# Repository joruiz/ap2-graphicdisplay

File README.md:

ap2-graphicdisplay
==================

Graphic display module for the Agile Prototyping Platform

  This work has been supported by project grant CEN-20101019 (THOFU), funded
by the Spanish Centro para el Desarrollo Tecnol ogico Industrial (CDTI) and
supported by the Spanish Ministerio de Economía y Competitividad.

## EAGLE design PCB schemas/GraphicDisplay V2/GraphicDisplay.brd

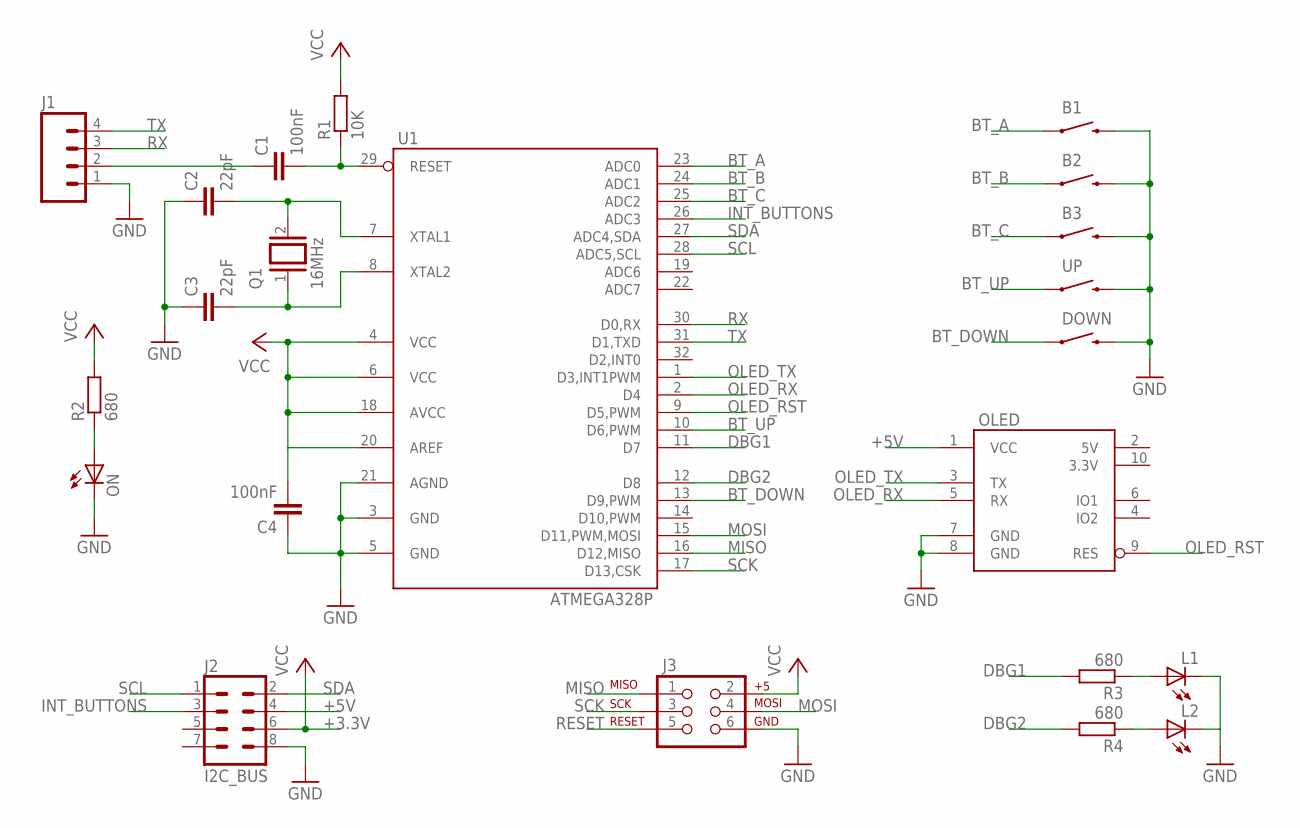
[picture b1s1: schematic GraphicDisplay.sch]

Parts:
B1, B2, B3: SWITCH-MOMENTARY-212MM; TACTILE-PTH-12MM
C1, C4: 100nF; C0805
C2, C3: 22pF; C0805
DOWN: SWITCH-MOMENTARY-212MM; TACTILE-PTH-12MM
J1: M04PTH; 1X04
J2: I2C_BUS; SOCKET04X2_ANGLE
J3: AVR_SPI_PRG_6NS; 2X3-NS
L1, L2: LEDCHIP-LED0805; CHIP-LED0805
OLED: UOLED-160-G2
ON: LEDCHIP-LED0805; CHIP-LED0805
Q1: 16MHz; QS
R1: 10K; R0805
R2, R3, R4: 680; R0805
U1: ATMEGA328P; TQFP32-08
UP: SWITCH-MOMENTARY-212MM; TACTILE-PTH-12MM

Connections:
3.3V: OLED.10 (3.3V)
5V: OLED.2 (5V)
+5V: J2.4, OLED.1 (VCC)
BT_A: B1.1, U1.23 (ADC0)
BT_B: B2.1, U1.24 (ADC1)
BT_C: B3.1, U1.25 (ADC2)
BT_DOWN: DOWN.1, U1.13 (D9,PWM)
BT_UP: U1.10 (D6,PWM), UP.1
DBG1: R3.2, U1.11 (D7)
DBG2: R4.2, U1.12 (D8)
GND: B1.3 (2), B2.3 (2), B3.3 (2), C2.1, C3.1, C4.1, DOWN.3 (2), J1.1, J2.8, J3.6, L1.C, L2.C, OLED.7 (GND), OLED.8 (GND), ON.C, U1.3 (GND), U1.5 (GND), U1.21 (AGND), UP.3 (2)
INT_BUTTONS: J2.3, U1.26 (ADC3)
MISO: J3.1, U1.16 (D12,MISO)
MOSI: J3.4, U1.15 (D11,PWM,MOSI)
unnamed: C1.1, J1.2
unnamed: C2.2, Q1.2, U1.7 (XTAL1)
unnamed: C3.2, Q1.1, U1.8 (XTAL2)
unnamed: ON.A, R2.1
unnamed: L1.A, R3.1
unnamed: L2.A, R4.1
OLED_RST: OLED.9 (RES), U1.9 (D5,PWM)
OLED_RX: OLED.5 (RX), U1.2 (D4)
OLED_TX: OLED.3 (TX), U1.1 (D3,INT1PWM)
RESET: C1.2, J3.5, R1.1, U1.29 (RESET)
RX: J1.3, U1.30 (D0,RX)
SCK: J3.3, U1.17 (D13,CSK)
SCL: J2.1, U1.28 (ADC5,SCL)
SDA: J2.2, U1.27 (ADC4,SDA)
TX: J1.4, U1.31 (D1,TXD)
VCC: C4.2, J2.6, J3.2, R1.2, R2.2, U1.4 (VCC), U1.6 (VCC), U1.18 (AVCC), U1.20 (AREF)

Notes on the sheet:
+3.3V

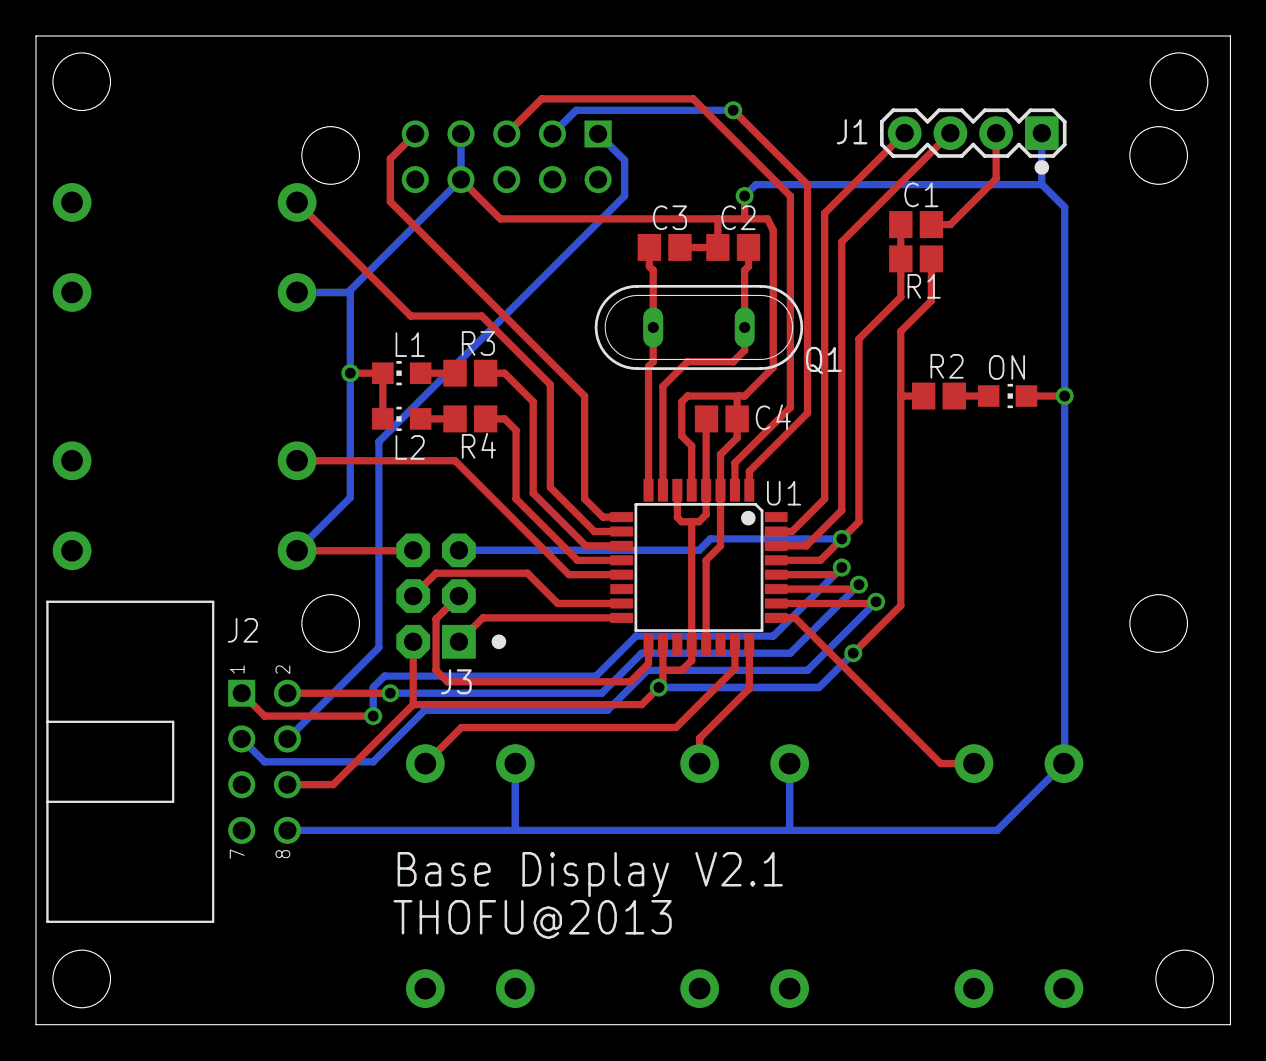
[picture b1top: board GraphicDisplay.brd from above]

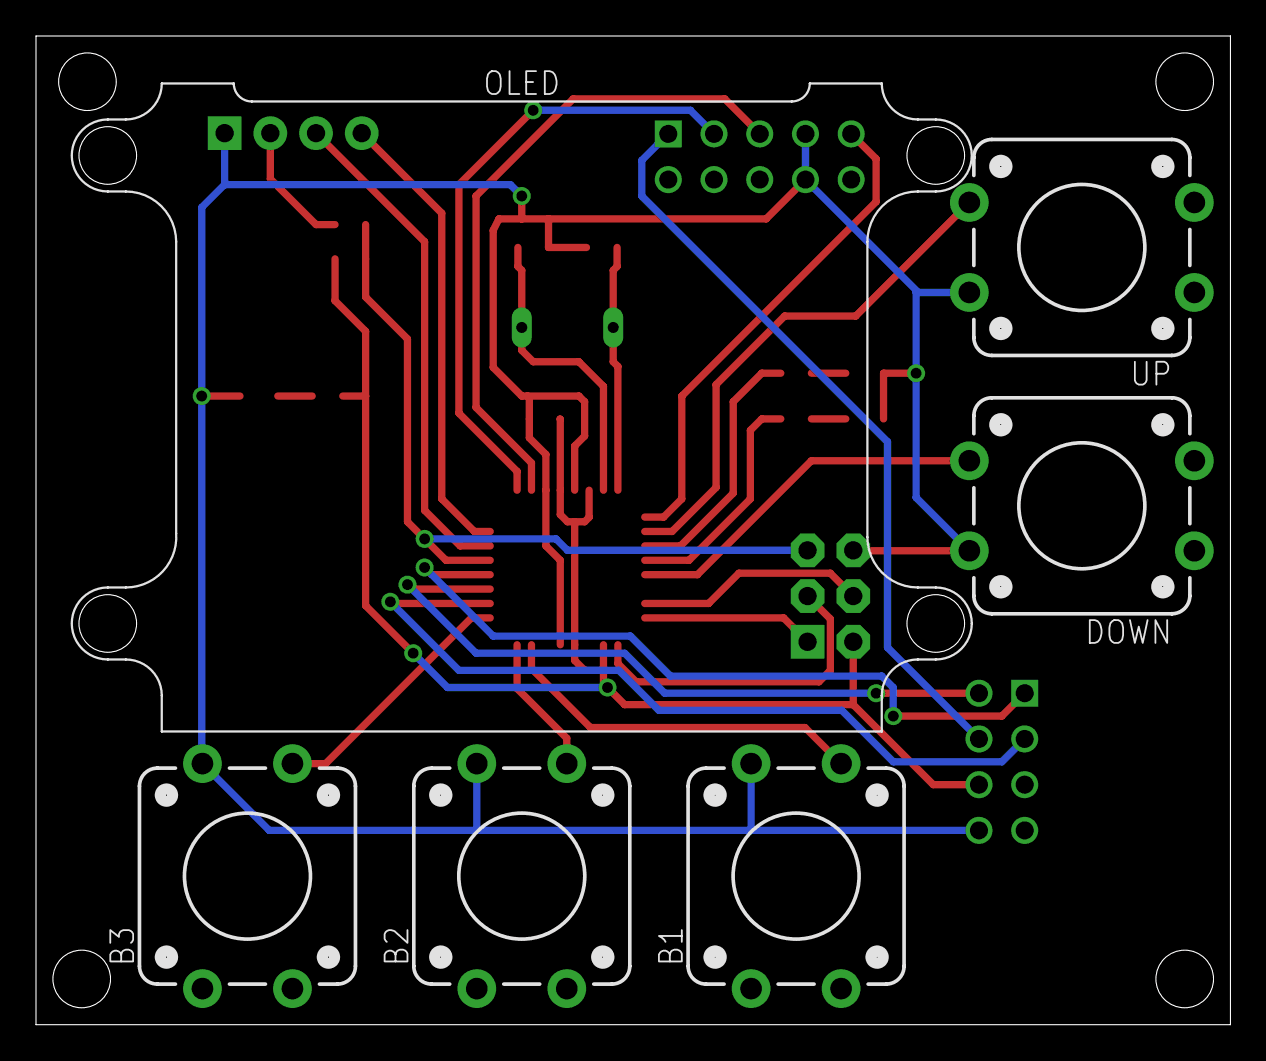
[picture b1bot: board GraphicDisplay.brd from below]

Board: 2 copper layers, 66.4 x 54.9 mm, 22 parts (6 on the bottom side), 28 nets.

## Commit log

2014-06-05 Added Version 1 of the graphic display peripheral
2014-06-26 Solved LoadImageFromSD example error

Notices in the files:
parts and their libraries:
SparkFun-Connectors: Licensing: CC v3.0 Share-Alike You are welcome to use this library for commercial purposes.
